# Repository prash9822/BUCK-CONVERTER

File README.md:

# BUCK-CONVERTER
 Buck converter - Wikipedia A buck converter or step-down converter is a DC-to-DC converter which steps down voltage (while stepping up current) from its input (supply) to its output (load).

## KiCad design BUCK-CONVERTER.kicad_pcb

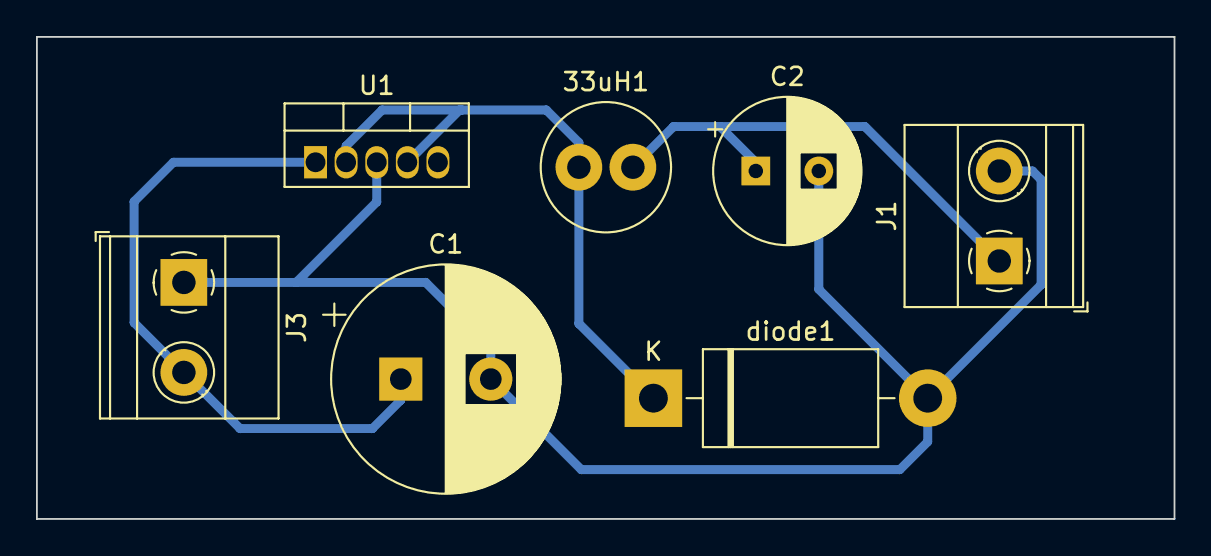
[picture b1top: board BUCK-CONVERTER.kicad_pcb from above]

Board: 2 copper layers, 63.2 x 26.8 mm, 7 parts (0 on the bottom side), 4 nets.

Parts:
33uH1: L; L_Radial_D7.0mm_P3.00mm
C1: 680uf; CP_Radial_D12.5mm_P5.00mm
C2: C_Polarized; CP_Radial_D8.0mm_P3.50mm
J1, J3: Screw_Terminal_01x02; TerminalBlock_Phoenix_MKDS-1,5-2_1x02_P5.00mm_Horizontal
U1: LM2596S-5; TO-220-5_Vertical
diode1: 1N5820; D_DO-201AD_P15.24mm_Horizontal

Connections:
GND: C1.2, C2.2, J1.2, J3.1, U1.3 (GND), U1.5 (~ON/OFF), diode1.2 (A)
unnamed: 33uH1.2, C2.1, J1.1
unnamed: C1.1, J3.2, U1.1 (VIN)
unnamed: 33uH1.1, U1.2 (OUT), U1.4 (FB), diode1.1 (K)

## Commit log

2023-10-05 Create IMAGES
